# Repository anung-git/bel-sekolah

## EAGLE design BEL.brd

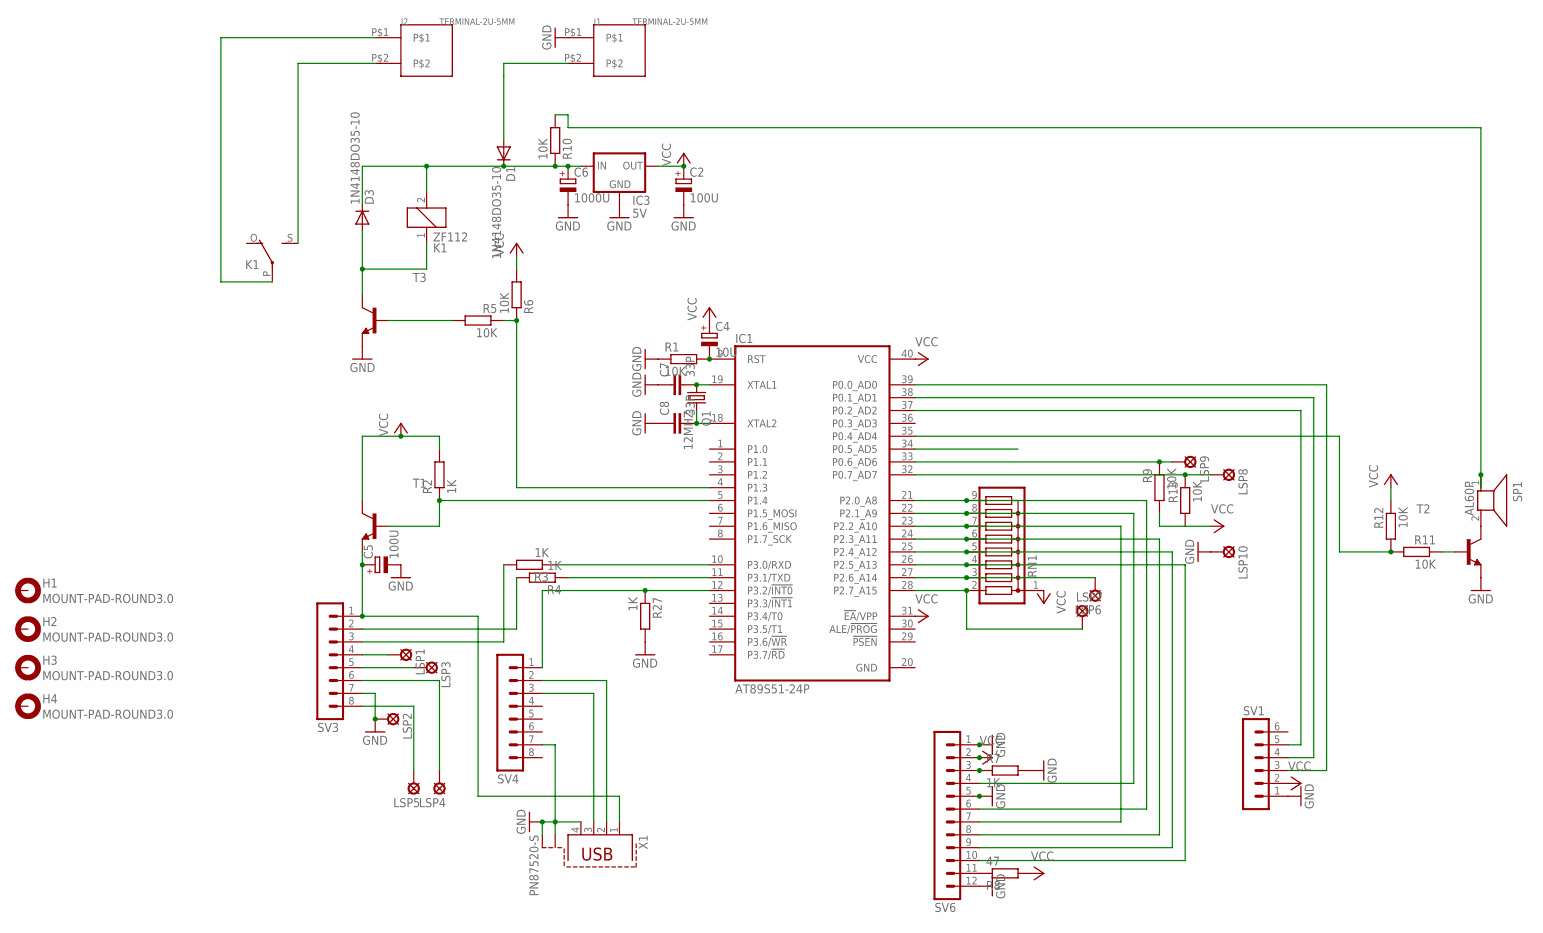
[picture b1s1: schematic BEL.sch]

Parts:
C2, C5: 100U; E2,5-5
C4: 10U; E2,5-5
C6: 1000U; E5-8,5
C7, C8: 33P; C025-025X050
D1, D3: 1N4148DO35-10; DO35-10
H1, H2, H3, H4: MOUNT-PAD-ROUND3.0; 3,0-PAD
IC1: AT89S51-24P; DIL40
IC3: 5V; 78XXS
J1, J2: TERMINAL-2U-5MM
K1: ZF112
LSP1, LSP2, LSP3, LSP4, LSP5: SE11
LSP6, LSP7, LSP8, LSP9, LSP10: MCS10B
Q1: 12MHZ; HC49/S
R1, R5, R6, R9, R10, R11, R12, R13: 10K; 0207/10
R2, R3, R4, R7, R27: 1K; 0207/10
R8: 47; 0207/10
RN1: G08R; SIL9
SP1: AL60P
SV1: MA06-1
SV3, SV4: MA08-1
SV6: MA12-1
T1, T2, T3: BC547-NPN-TO92-CBE; TO92-CBE
X1: PN87520-S

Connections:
GND: C2.-, C5.-, C6.-, C7.1, C8.1, IC1.20 (GND), IC3.GND, J1.P$1, LSP2.MP, LSP10.MP, R1.1, R7.2, R27.2, SV1.1, SV3.7, SV4.7, SV6.1, SV6.5, SV6.12, T2.E, T3.E, X1.4, X1.S1, X1.S2
unnamed: C8.2, IC1.18 (XTAL2), Q1.2
unnamed: C7.2, IC1.19 (XTAL1), Q1.1
unnamed: C4.-, IC1.9 (RST), R1.2
unnamed: R10.2, SP1.1
unnamed: D3.A, K1.1, T3.C
unnamed: C5.+, SV3.1, T1.E, X1.1
unnamed: IC1.5 (P1.4), R2.1, T1.B
unnamed: SP1.2, T2.C
unnamed: R4.2, SV3.2
unnamed: R3.2, SV3.3
unnamed: IC1.11 (P3.1/TXD), R4.1
unnamed: IC1.10 (P3.0/RXD), R3.1
unnamed: IC1.12 (P3.2/!INT0), R27.1, SV4.1
unnamed: IC1.26 (P2.5_A13), RN1.4, SV6.10
unnamed: IC1.38 (P0.1_AD1), SV1.4
unnamed: SV4.2, X1.2
unnamed: SV4.3, X1.3
unnamed: LSP4.MP, SV3.6
unnamed: IC1.23 (P2.2_A10), RN1.7, SV6.7
unnamed: R5.2, T3.B
unnamed: IC1.4 (P1.3), R5.1, R6.1
unnamed: D1.A, J1.P$2
unnamed: J2.P$2, K1.S
unnamed: J2.P$1, K1.P
unnamed: IC1.37 (P0.2_AD2), SV1.5
unnamed: R7.1, SV6.3
unnamed: IC1.39 (P0.0_AD0), SV1.3
unnamed: R11.1, T2.B
unnamed: C6.+, D1.C, D3.C, IC3.IN, K1.2, R10.1
unnamed: LSP5.MP, SV3.8
unnamed: LSP1.MP, SV3.4
unnamed: LSP3.MP, SV3.5
unnamed: R8.1, SV6.11
unnamed: IC1.24 (P2.3_A11), RN1.6, SV6.8
unnamed: IC1.21 (P2.0_A8), RN1.9, SV6.6
unnamed: IC1.22 (P2.1_A9), RN1.8, SV6.4
unnamed: IC1.35 (P0.4_AD4), R11.2, R12.2
unnamed: IC1.33 (P0.6_AD6), LSP9.MP, R9.1
unnamed: IC1.32 (P0.7_AD7), LSP8.MP, R13.1
unnamed: IC1.28 (P2.7_A15), LSP7.MP, RN1.2
unnamed: IC1.27 (P2.6_A14), LSP6.MP, RN1.3
unnamed: IC1.25 (P2.4_A12), RN1.5, SV6.9
VCC: C2.+, C4.+, IC1.31 (!EA!/VPP), IC1.40 (VCC), IC3.OUT, R2.2, R6.2, R8.2, R9.2, R12.1, R13.2, RN1.1, SV1.2, SV6.2, T1.C

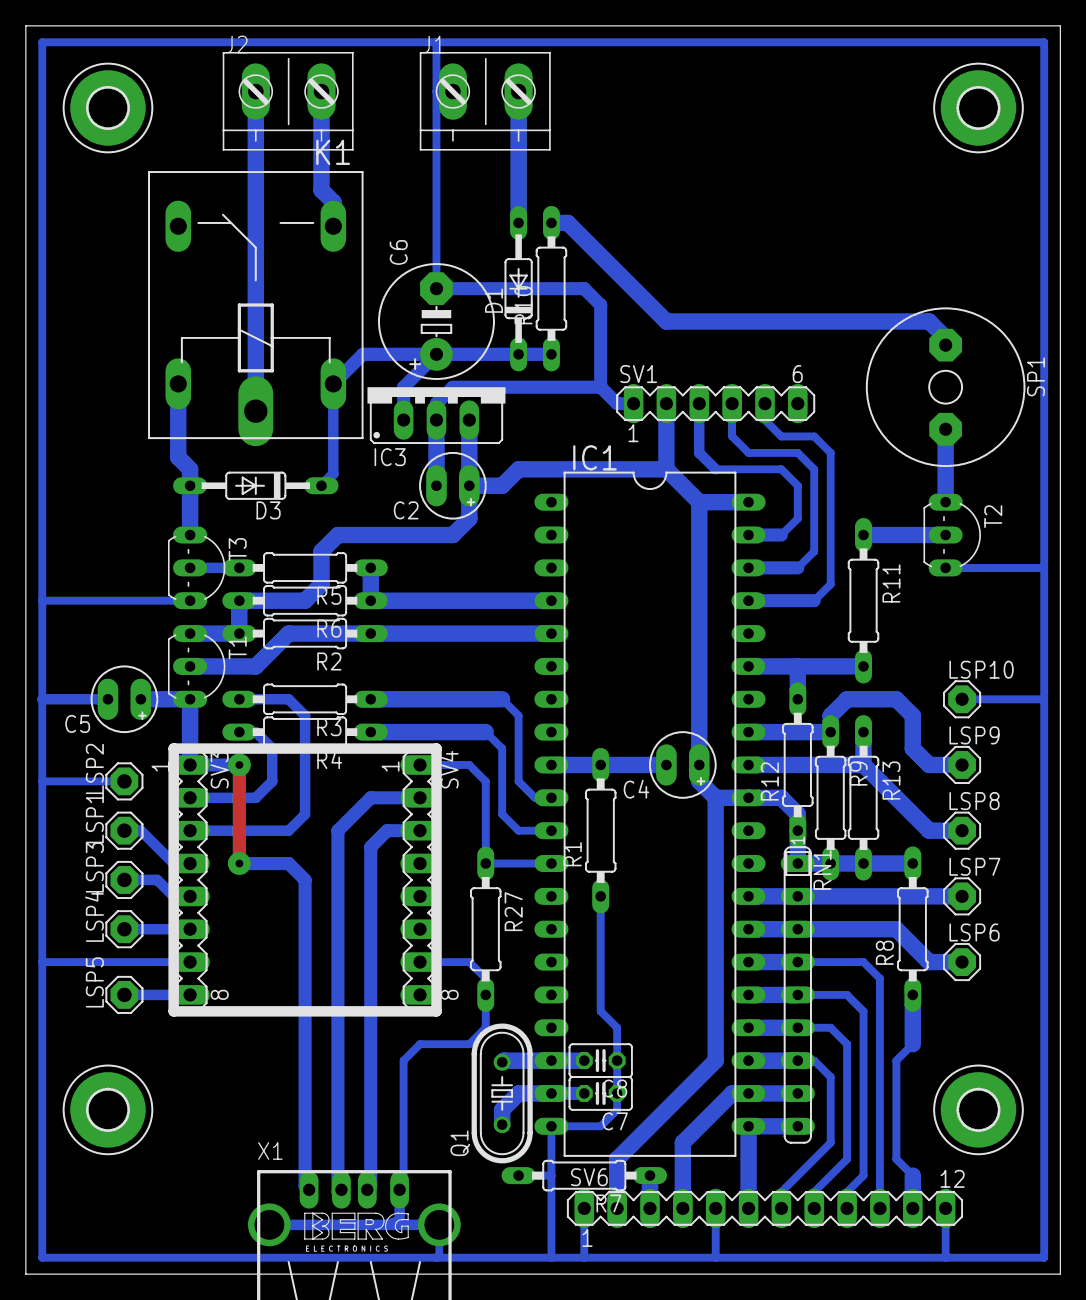
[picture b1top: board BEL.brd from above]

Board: 2 copper layers, 80.0 x 96.5 mm, 52 parts (0 on the bottom side), 44 nets.

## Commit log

2019-09-15 upload file
